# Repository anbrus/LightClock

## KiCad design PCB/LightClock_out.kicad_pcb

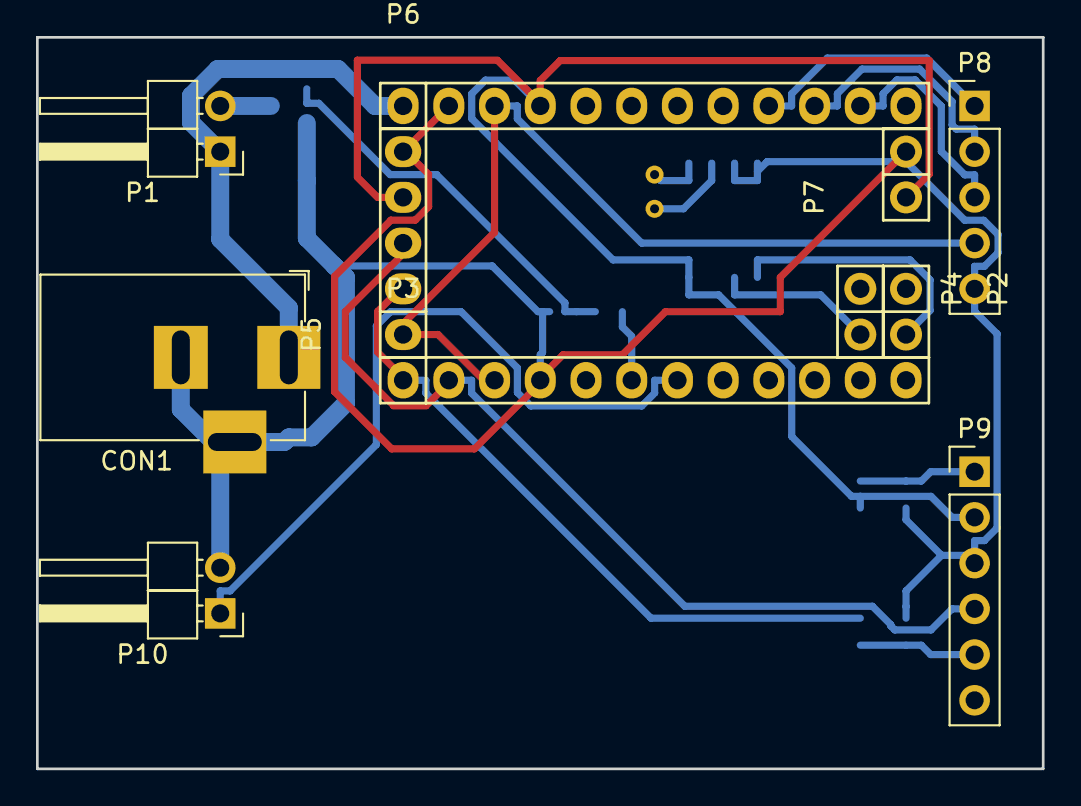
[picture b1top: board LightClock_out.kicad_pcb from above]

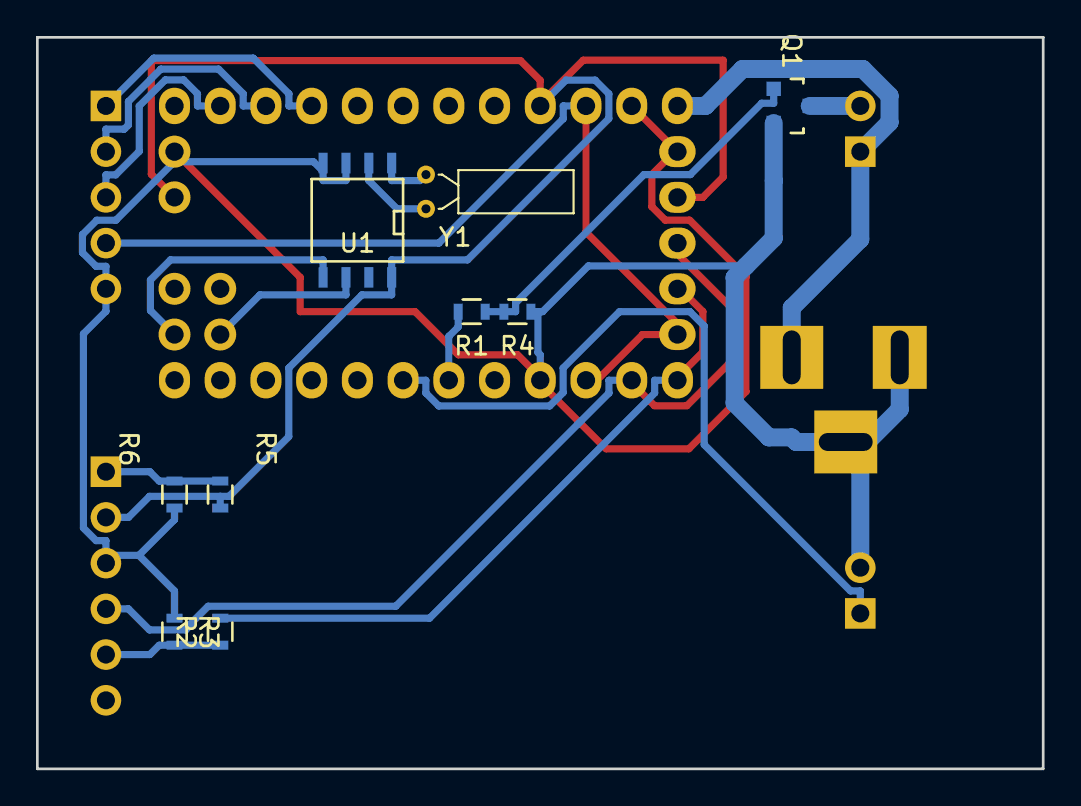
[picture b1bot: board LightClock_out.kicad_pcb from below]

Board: 2 copper layers, 55.9 x 40.6 mm, 20 parts (9 on the bottom side), 19 nets.

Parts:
CON1: PWR; BarrelJack_Horizontal
P1: Light; Pin_Header_Angled_1x02_Pitch2.54mm
P2, P4: ADC; Socket_Strip_Arduino_1x02
P3: Digital; Socket_Strip_Arduino_1x12
P5: COM; Socket_Strip_Arduino_1x05
P6: Analog; Socket_Strip_Arduino_1x12
P7: PWR; Socket_Strip_Arduino_1x02
P8: PROG; Pin_Header_Straight_1x05_Pitch2.54mm
P9: BT; Pin_Header_Straight_1x06_Pitch2.54mm
P10: Off; Pin_Header_Angled_1x02_Pitch2.54mm
Q1: IRLML6244TRPbF; SOT-23
R1: 200; R_0603
R2, R5: 510; R_0603
R3, R6: 1000; R_0603
R4: 10 kOhm; R_0603
U1: DS1307+; SOIC-8-N
Y1: Crystal_Small; Crystal_DS26_D2.0mm_L6.0mm_Horizontal

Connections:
+5V: P5.4, P6.4, P7.1, P9.2, R5.2, U1.8
+12V: CON1.1, P1.1, P6.1
/0(Rx): P3.2, P5.3, P9.4
/1(Tx): P3.1, P5.2, R2.2
/3(**): P3.6, R1.2
/4: P3.7, P10.1
/11(MISO): P6.11, P8.3
/12(**/MOSI): P6.10, P8.2
/13(SCK): P6.9, P8.1
/A4: P2.2, U1.5
/A5: P4.2, U1.6
/Reset: P3.3, P5.1, P6.3, P8.4
GND: CON1.2, CON1.3, P3.4, P5.5, P6.2, P7.2, P8.5, P9.3, P10.2, Q1.2, R3.1, R4.1, R6.1, U1.3, U1.4
unnamed: P1.2, Q1.3
unnamed: P9.1, R5.1, R6.2
unnamed: P9.5, R2.1, R3.2
unnamed: Q1.1, R1.1, R4.2
unnamed: U1.1, Y1.2
unnamed: U1.2, Y1.1

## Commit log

2017-12-23 Исправлена высота корпуса
